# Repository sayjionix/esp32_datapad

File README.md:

# ESP32 Datapad & Jira Timelogger Introduction
The __ESP32 Datapad & Jira Timelogger__ is a handheld ESP32-based keypad with 20 keys, a 20x4 character LCD display and a provision for operating from a single 3,7V LiPo cell. While the __Datapad__ hardware can generally be used for multiple purposes and provides a universal hardware development platform, the __timelogger__ firmware specifically allows tracking and logging time to [__Jira__](https://www.atlassian.com/software/jira).

The main features are:
* Connect the Datapad with your Atlassian Jira account using the REST API
* Map up to 16 favorite Jira tasks to the physical keys of the Datapad
* Tap a key once to start logging your time, tap again to stop logging and transfer the time to Jira
* Seamlessly switch over from logging on one task to another
* Manually enter spent time to book to your task
* Supports configuration of 2 WiFis to use the Datapad at two locations, e.g. at home and at workplace
* NTP-based time synchronization
* Use the Datapad as a development platform for your own keypad projects

# Build Instructions
Build your own Datapad! It's fun! :)

## BOM
The following table provides a BOM with Mouser and Reichelt part numbers.

| Part     | Pcs | Type / Value                     | Mouser PN            | Reichelt PN        |
|----------|:---:|----------------------------------|----------------------|--------------------|
|          | 1   | LCD Display 20x4                 | 763-0420AZFSWGBW33V3 |                    |
|          | 1   | Olimex ESP32-S3-DevKit-Lipo      | 909-ESP32S3DEVKITLIP |                    |
| SW1-SW20 | 20  | Cherry MX Switch                 | 540-MX2A-E1NW        | CHERRY MX2A-E1NW   |
| D1-D20   | 20  | Diode 1N4148                     | 512-1N4148           | 1N 4148            |
| Q1       | 1   | Transistor NPN BC548             | 637-BC548B           | BC 548C            |
| RV1      | 1   | Trim Poti 10k flat               |                      | 64P-10K            |
| RV2      | 1   | Trim Poti 2k flat                |                      | 64P-2,0K           |
| J1       | 1   | JST PH2P Socket                  |                      | JST PH2P ST90      |
| J2       | 1   | Pin Socket 1x16, 2,54mm, THT     | 855-M20-7821646      |                    |
|          | 1   | Pin Header 1x16, 2,54mm, THT     |                      |                    |
|          | 2   | Pin Header 1x22, 2,54mm, THT     |                      |                    |
| R3       | 1   | Resistor 1/4W, 27k               |                      |                    |
| R4       | 1   | Resistor 1/4W, 0R                |                      |                    |
| SW21     | 1   | On-Off Switch                    | 611-OS102011MA1QN1   |                    |
|          | 1   | LiPo Battery 3,7V, >= 100mAh     |                      |                    |
|          | 4   | 11mm Hexagonal Spacer or similar |                      |                    |

## Ordering and populating the PCB
The PCB can be ordered at any PCB manufacturer, such as [JLCPCB](https://jlcpcb.com/) or [PCBWay](https://www.pcbway.com/). In the [pcb/Datapad/fab/](pcb/Datapad/fab/) directory, there is a ZIP file with the Gerber and drill files, that can be used as-is to upload it to the manufacturer. For most manufacturers, you can likely leave all order options with their default values.

Soldering the components to the PCB should be simple, as the project only uses through-hole components. A generic tip is, to start with the small and flat parts first, such as the diodes and resistors, and then progress with the more bulky parts, such as the Cherry MX switches.

Solder the two 1x22 pin headers to the bottom of the Olimex ESP32 board and solder the 1x16 pin header to the bottom of the LCD display.

It is recommended to solder the ESP32 with the attached pin headers to the main PCB as flush as possible to have enough clearance for the LCD display. Also, solder the ESP32 to the main PCB as one of the last steps. This way, you don't "lose" the ESP32 board in case any other step of the soldering goes wrong.

To power the ESP32 board from battery, solder a cable between the JST connector on the board and the Datapad PCB. Attach the battery with it's connector to the socket on the Datapad PCB.

## Programming the ESP32
This project is built and optimized using the PlatformIO ecosystem.

1. Download and install [VS Code](https://code.visualstudio.com/).
2. Install the PlatformIO IDE module directly from the VS Code Extensions Marketplace.
3. Connect the ESP32 board up to your PC with the right-side USB-C connector (when looking to the front of the USB ports. Labeled "USB-UART1").
4. Access the PlatformIO sidebar menu (represented by the Ant icon on the left panel grid) and open the timelogger project in the folder that contains the _platformio.ini_
5. Click the "Upload" action button (represented by the right-facing horizontal arrow icon along the bottom window status bar).
6. Wait for the code to be compiled and uploaded to the ESP32 via it's serial bootloader.

## 3D-printed Parts
There are *.stl files available in the [mechanical/](mechanical/) directory for two different variants of housings.

For the Cherry MX Keycaps, the following free online model is recommended. However, any Cherry MX compatible keycaps can be used.<br>
https://makerworld.com/de/models/132469-xda-style-keycaps-blank#profileId-143606

# Operating Manual
## Keypad Layout

## Energy Saving
After 60 seconds of inactivity, the Datapad will turn off the LCD display and backlight and it will bring the ESP32 into light sleep mode. Any running timers will keep on running in the background. To wake the Datapad up again, simply press any key on the keypad. This keypress will not trigger any action other than waking up.

## Display settings
Use the two potentiometers to adjust display contrast and backlight intensity.

## Battery operation
The On/Off switch on the top of the Datapad connects/disconnects the battery from the circuit. That means:

* to charge the battery from USB, make sure the On/Off switch is set to "On".
* the Datapad will be powered independently of the On/Off switch, once any of the two USB-C ports is connected to a power source.

## Base configuration
The basic configuration of the Datapad is performed via a serial terminal connection to your PC. You can use the same USB-C connection that you used for programming the ESP32 board and either utilize PlatformIO's Serial Monitor feature or any other serial terminal program of your choice. The serial setting are 115200baud, 8N1.

The basic configuration via the serial terminal includes:
1. WiFi 1 Name (SSID)
2. WiFi 1 Password
3. WiFi 2 Name (SSID)
4. WiFi 2 Password
5. Jira-Host
6. Base64 Credentials
7. Max Timer Duration

If the Datapad is started the first time and there is no configuration yet, it will prompt you to connect to your PC. The firmware can not start without the basic setup and having at least WiFi 1 configured and the Jira-Host and the Base64 Credentials set.

You can re-enter the basic configuration again at any time by pressing and holding the _SHIFT_ key + _ENTER_ key, while turning on the Datapad.

Troubleshooting: If you don't see any output in the terminal, try sending anything (except a number between 1-8) to the Datapad. The firmware will reject this as an invalid choice for the main menu and re-render the main menu.

### Create your base64 credentials from your Jira API Token
A base64 representation of your Jira API token is required to access Jira's REST API. To get this, you have to perform the following steps:

1. Generate an API token for Jira using your Atlassian Account. Go to your account settings -> Security -> API Token.
2. Build a string of the form useremail:api_token.
3. BASE64 encode the string.

   Linux/Unix/MacOS:
   ```
   echo -n "user@example.com:api_token_string" | base64
   ```

   Windows 7 and later, using Microsoft Powershell:
   ```
   $Text = ‘user@example.com:api_token_string’
   $Bytes = [System.Text.Encoding]::UTF8.GetBytes($Text)
   $EncodedText = [Convert]::ToBase64String($Bytes)
   $EncodedText
   ```
4. Make sure that your resulting base64 string doesn't contain any unwanted carriage returns or other whitespace characters when you copy them to your Datapad configuration via the terminal. Unwanted whitespace characters are a common reason why the Jira login does not work later on. It can be easily checked by pasting the resulting base64 string into a text editor that can show whitespace characters, such as notepad++.

## Jira task mapping
If the Datapad starts with a valid configuration, it will show a 4x4 matrix of your 16 favorite Jira IDs on the LCD display (each Jira ID is consisting of the alphanumeric Jira key, followed by an unique number, e.g. "MGMT-2"). This 4x4 matrix corresponds to the lower 4x4 segment of the physical keypad.

If no Jira IDs have been mapped yet, each cell of the matrix will show "****".<br>

Once Jira IDs have been mapped to the 4x4 matrix, the Datapad will periodically cycle through indicating the Jira key and the unique identifier at the given cell on the LCD display.<br>

### Map a Jira task ID to a physical key
To map a new Jira task to any of the free slots of your 4x4 matrix of favorites, simply press and hold the _SHIFT_ key and then press the key that corresponds to the slot you like to map. A dialog will show on the LCD display that prompts you for the Jira ID. The Jira ID can be entered using the T9-feature of the keypad. Each Jira ID is consisting of the alphanumeric Jira key, followed by an unique number, e.g. "MGMT-2".

To correct a typing mistake or to exit the dialog completely, simply press _CANCEL_ (repeatedly).
To conclude your entry and map the Jira ID, press _ENTER_. The Datapad will call the REST API to fetch information about the task, such as the task's name. If the task can not be found or there is any other issue with the connection to your Jira server, the mapping will be completed, calling the task "Unknown Task". 

### Remove a Jira task ID from a physical key
To remove a Jira task from the 4x4 matrix of favorites, simply press and hold the _CANCEL_ key before pressing the key of the task you like to remove. A confirmation dialoge will prompt you to either continue by pressing _ENTER_, or to cancel the removal by pressing _CANCEL_.

Once the Jira task is removed, the slot becomes free again and is displayed as "****".

### Show task name
When mapping a Jira task to one of the slots of the 4x4 matrix, the Datapad will try to obtain the task's name via the Jira REST API. To display the name of a task in your 4x4 matrix, simply press and hold the _ENTER_ key before pressing the key of the task you like to show. This can be helpful when you are unsure to recognize the right task just judging from the Jira ID.

## Log time
There are two ways to log time to your Jira tasks.

### Automatic timer mode
A worklog timer can be started for any of the Jira tasks from the 4x4 matrix of favorites by simply pressing the key that corresponds to the task you like to log. Once the timer has started, the LCD display switches to an indication of the running timer. To stop a running timer, press the according task key again. A dialog will prompt you to confirm whether you would like to log the recorded timer to Jira. Press the _ENTER_ key once you are ready to log the time. The Datapad will then transmit the time to Jira via the REST API and automatically calculate the starting time of the activity based on the recorded minutes. Press _CANCEL_ to discard the recorded time.

If you start a timer in parallel on a different Jira task, the Datapad will automatically stop the previously running timer and prompt you, whether to keep or discard the recording of the previous timer. It will then start the new timer.

Timers can only be started on non-empty slots.

### Direct entry
Time can also be entered directly to be logged to a certain Jira task. This is helpful if you forgot to start the timer before you started working on your activity and you would like to restrospecively log the time.

Press and hold _DIRECT_ and then press the key that corresponds to the task you like to log to. A dialog will prompt you to enter the time in minutes using the numeric keys. Press the _CANCEL_ key to correct your entry or to completely cancel the direct time entry. Press the _ENTER_ key once you are ready to log the time. The Datapad will then transmit the time to Jira via the REST API and automatically calculate the starting time of the activity based on the entered minutes.

## Information Display
When pressing the _SHIFT_ and _INFO_ keys simultaneously while being in the 4x4 overview, the LCD display will show:
* Firmware version
* Battery voltage (when running from battery) or "USB connected" (when being powered from USB)
* Actual time and date. Time and date will be fetched via NTP every 3 hours. This is to compensate for the poor crystal accuracy of the ESP32 board and the clock drift that comes as a result

Press _CANCEL_ or _ENTER_ to return.

# Hardware Changelog
**v1.0, 31.05.2026:** First fab release of PCB.

# License
The Datapad Timelogger is released under the GNU GPLv3.<br>
Please refer to the [LICENSE](./LICENSE) file for more information.

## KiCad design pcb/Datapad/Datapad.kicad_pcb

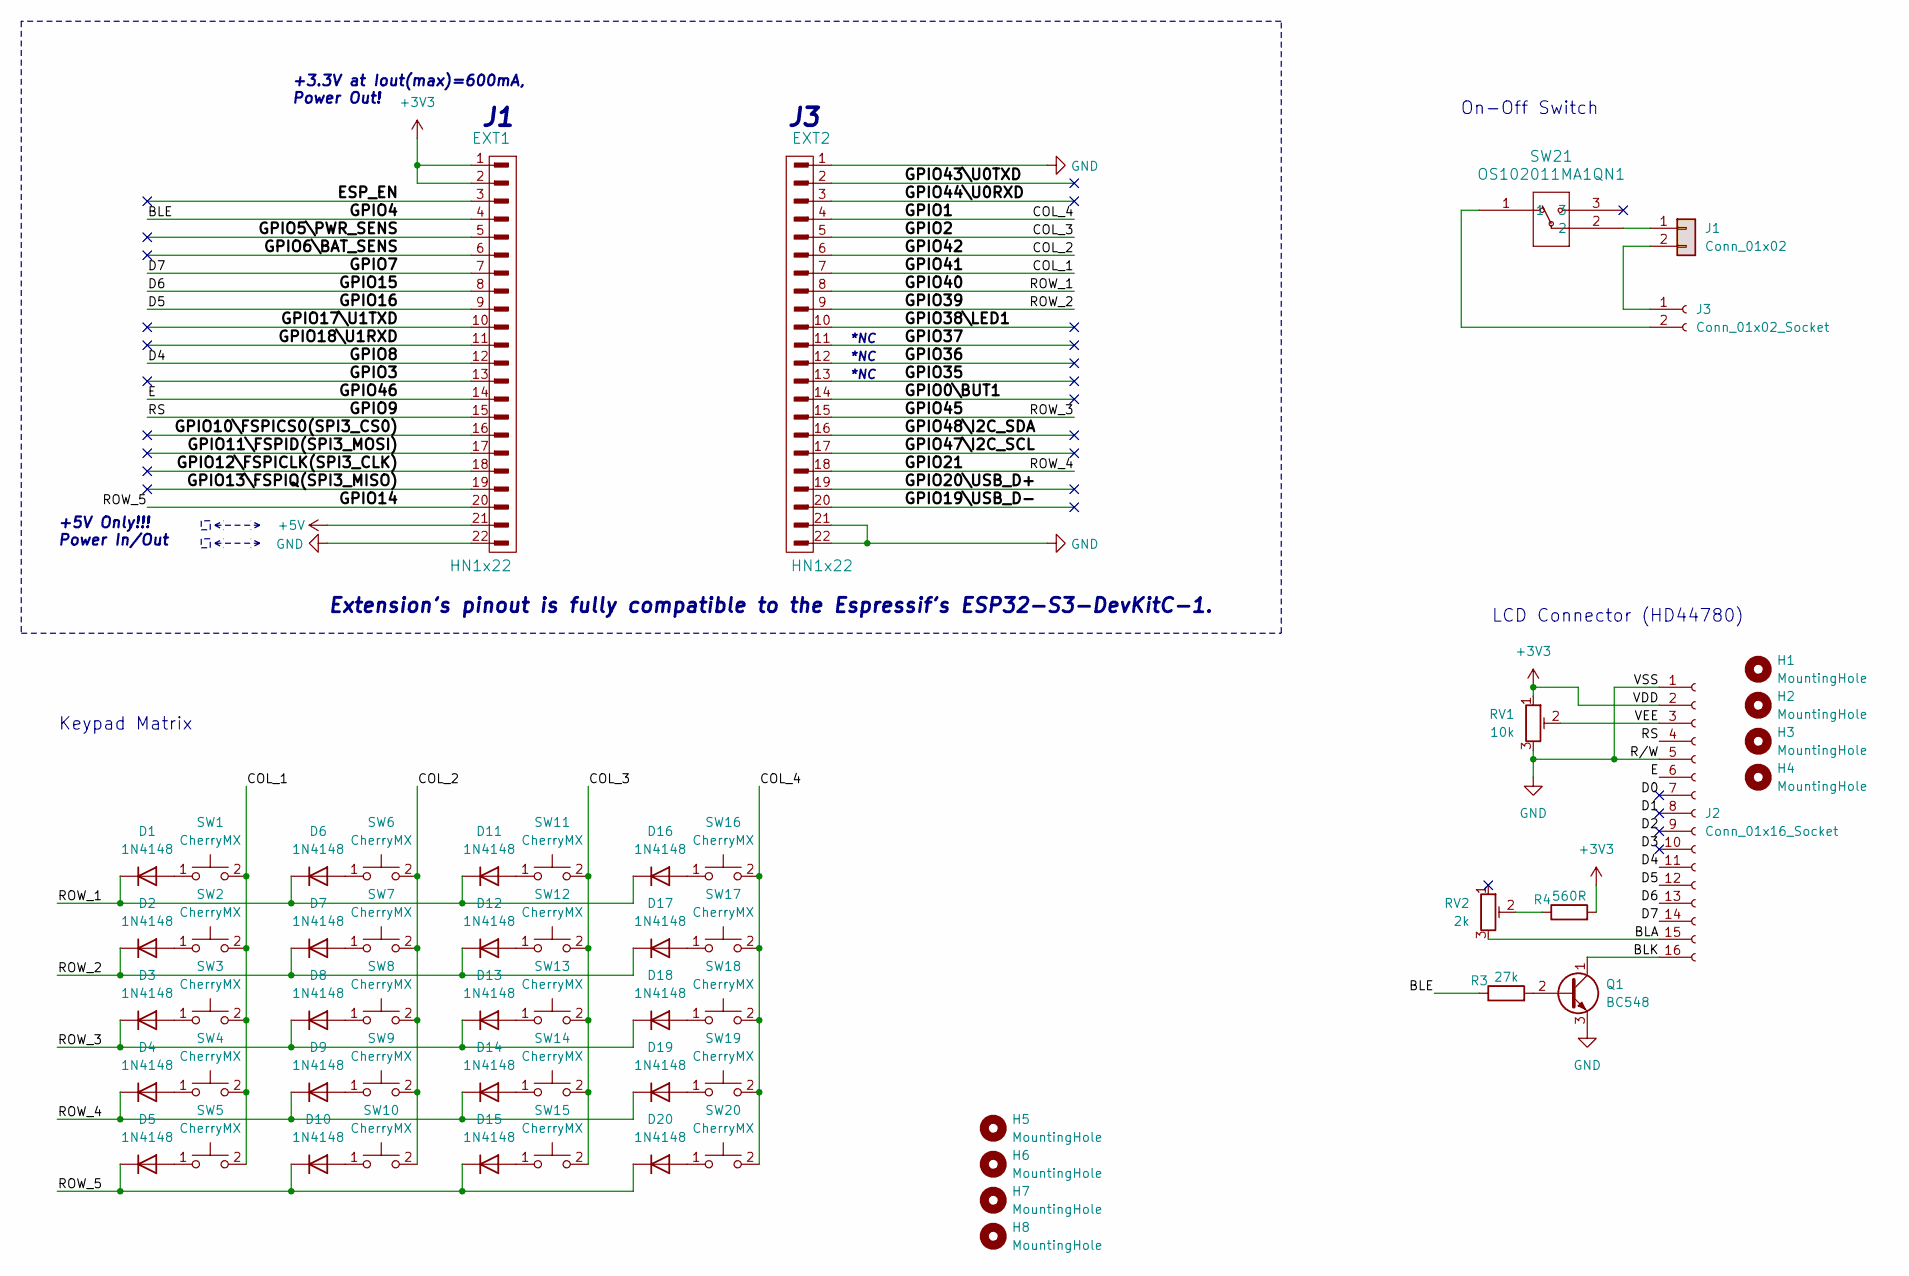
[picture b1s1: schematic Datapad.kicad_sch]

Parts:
D1, D2, D3, D4, D5, D6, D7, D8, D9, D10, D11, D12, D13, D14, D15, D16, D17, D18, D19, D20: 1N4148; D_DO-35_SOD27_P7.62mm_Horizontal
EXT1, EXT2: HN1x22; PinSocket_1x22_P2.54mm_Vertical
H1, H2, H3, H4: MountingHole; MountingHole_4mm
H5, H6, H7, H8: MountingHole; MountingHole_2.7mm
J1: Conn_01x02; JST_PH_S2B-PH-K_1x02_P2.00mm_Horizontal
J2: Conn_01x16_Socket; PinSocket_1x16_P2.54mm_Vertical
J3: Conn_01x02_Socket; PinSocket_1x02_P2.54mm_Vertical
Q1: BC548; TO-92_Inline
R3: 27k; R_Axial_DIN0207_L6.3mm_D2.5mm_P10.16mm_Horizontal
R4: 560R; R_Axial_DIN0207_L6.3mm_D2.5mm_P10.16mm_Horizontal
RV1: 10k; Potentiometer_Bourns_3296P_Horizontal
RV2: 2k; Potentiometer_Bourns_3296P_Horizontal
SW1, SW2, SW3, SW4, SW5, SW6, SW7, SW8, SW9, SW10, SW11, SW12, SW13, SW14, SW15, SW16, SW17, SW18, SW19, SW20: CherryMX; SW_Cherry_MX_1.00u_PCB
SW21: OS102011MA1QN1; OS102011MA1QN1_CNK

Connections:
+3V3: EXT1.1, EXT1.2, J2.2, R4.2, RV1.1
+5V: EXT1.21
/BLA: J2.15, RV2.3
/BLE: EXT1.4, R3.1
/BLK: J2.16, Q1.1 (C)
/COL_1: EXT2.7, SW1.2, SW2.2, SW3.2, SW4.2, SW5.2
/COL_2: EXT2.6, SW6.2, SW7.2, SW8.2, SW9.2, SW10.2
/COL_3: EXT2.5, SW11.2, SW12.2, SW13.2, SW14.2, SW15.2
/COL_4: EXT2.4, SW16.2, SW17.2, SW18.2, SW19.2, SW20.2
/D0: J2.7
/D1: J2.8
/D2: J2.9
/D3: J2.10
/D4: EXT1.12, J2.11
/D5: EXT1.9, J2.12
/D6: EXT1.8, J2.13
/D7: EXT1.7, J2.14
/E: EXT1.14, J2.6
/ESP_EN: EXT1.3
/GPIO0\BUT1: EXT2.14
/GPIO3: EXT1.13
/GPIO5\PWR_SENS: EXT1.5
/GPIO6\BAT_SENS: EXT1.6
/GPIO9: EXT1.15, J2.4
/GPIO10\FSPICS0(SPI3_CS0): EXT1.16
/GPIO11\FSPID(SPI3_MOSI): EXT1.17
/GPIO12\FSPICLK(SPI3_CLK): EXT1.18
/GPIO13\FSPIQ(SPI3_MISO): EXT1.19
/GPIO14: D5.1 (K), D10.1 (K), D15.1 (K), D20.1 (K), EXT1.20
/GPIO17\U1TXD: EXT1.10
/GPIO18\U1RXD: EXT1.11
/GPIO19\USB_D-: EXT2.20
/GPIO20\USB_D+: EXT2.19
/GPIO21: D4.1 (K), D9.1 (K), D14.1 (K), D19.1 (K), EXT2.18
/GPIO35: EXT2.13
/GPIO36: EXT2.12
/GPIO37: EXT2.11
/GPIO38\LED1: EXT2.10
/GPIO39: D2.1 (K), D7.1 (K), D12.1 (K), D17.1 (K), EXT2.9
/GPIO40: D1.1 (K), D6.1 (K), D11.1 (K), D16.1 (K), EXT2.8
/GPIO43\U0TXD: EXT2.2
/GPIO44\U0RXD: EXT2.3
/GPIO45: D3.1 (K), D8.1 (K), D13.1 (K), D18.1 (K), EXT2.15
/GPIO47\I2C_SCL: EXT2.17
/GPIO48\I2C_SDA: EXT2.16
/VEE: J2.3, RV1.2
GND: EXT1.22, EXT2.1, EXT2.21, EXT2.22, J2.1, J2.5, Q1.3 (E), RV1.3
unnamed: D1.2 (A), SW1.1
unnamed: D2.2 (A), SW2.1
unnamed: D3.2 (A), SW3.1
unnamed: D4.2 (A), SW4.1
unnamed: D5.2 (A), SW5.1
unnamed: D6.2 (A), SW6.1
unnamed: D7.2 (A), SW7.1
unnamed: D8.2 (A), SW8.1
unnamed: D9.2 (A), SW9.1
unnamed: D10.2 (A), SW10.1
unnamed: D11.2 (A), SW11.1
unnamed: D12.2 (A), SW12.1
unnamed: D13.2 (A), SW13.1
unnamed: D14.2 (A), SW14.1
unnamed: D15.2 (A), SW15.1
unnamed: D16.2 (A), SW16.1
unnamed: D17.2 (A), SW17.1
unnamed: D18.2 (A), SW18.1
unnamed: D19.2 (A), SW19.1
unnamed: D20.2 (A), SW20.1
unnamed: J1.1, SW21.2
unnamed: J1.2, J3.1
unnamed: J3.2, SW21.1
unnamed: Q1.2 (B), R3.2
unnamed: R4.1, RV2.2

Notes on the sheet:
+5V Only!!! Power In/Out
Keypad Matrix
+3.3V at Iout(max)=600mA, Power Out!
Extension's pinout is fully compatible to the Espressif's ESP32-S3-DevKitC-1.
*NC
On-Off Switch
LCD Connector (HD44780)

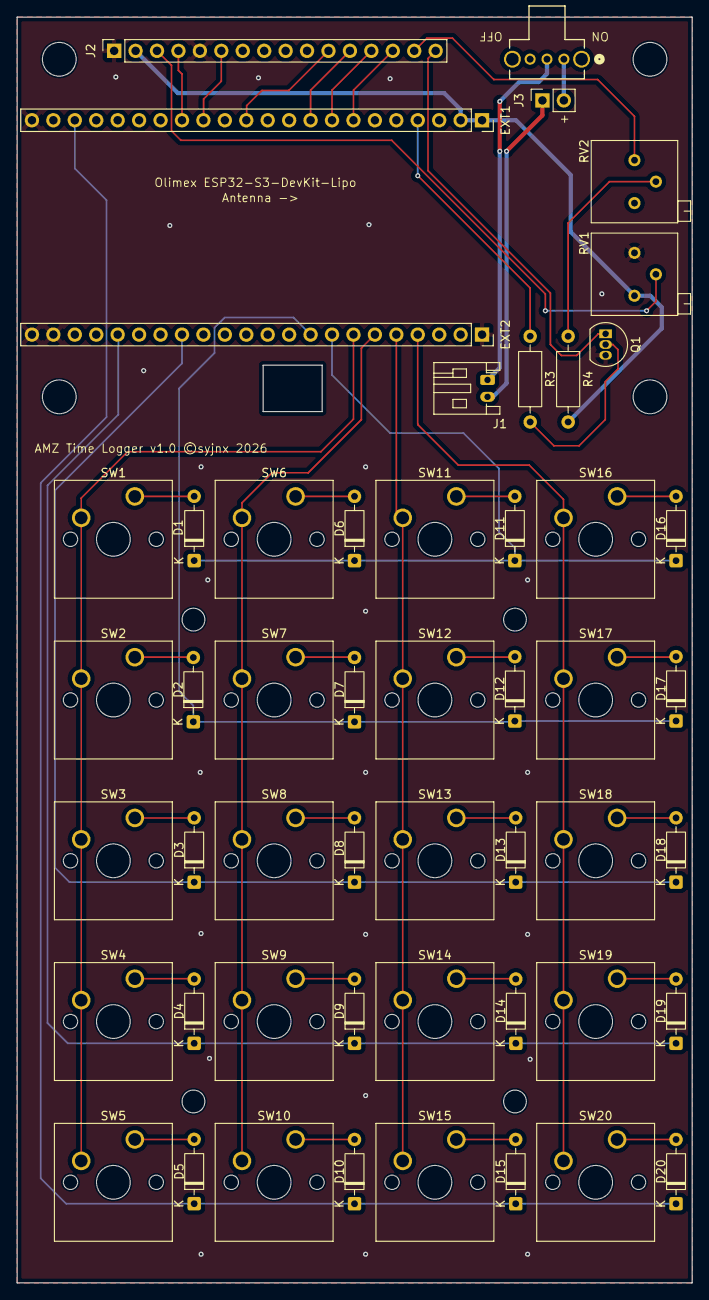
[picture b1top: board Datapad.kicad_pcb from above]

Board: 2 copper layers, 80.0 x 150.0 mm, 59 parts (0 on the bottom side), 46 nets.

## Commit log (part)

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2026-05-25 initial functionality to log 1h on task NBT-15 on press of a button
2026-05-25 untested: keypad matrix, T9 mode to reassign keys, long-press to directly book time, short-press to start timer
2026-05-25 untested: added HD44780 display (20x4)
2026-06-04 added support for displaying task names while logging
2026-06-04 adjusted pins to board design
2026-06-04 minor changes to comments
2026-06-16 made WiFi and Jira login data configurable
2026-06-16 temporary fix of rows and cols of keymatrix

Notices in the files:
pcb/Datapad/Datapad.kicad_pcb:
AMZ Time Logger v1.0 ©syjnx 2026
